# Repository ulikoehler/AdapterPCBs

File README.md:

# AdapterPCBs
Various open hardware adapter PCBs

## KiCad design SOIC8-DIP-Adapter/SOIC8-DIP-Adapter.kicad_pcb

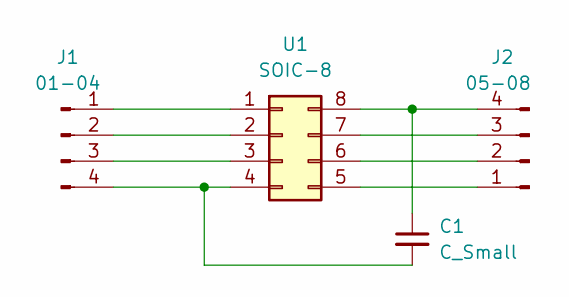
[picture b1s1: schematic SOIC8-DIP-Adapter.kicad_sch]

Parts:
C1: C_Small; C_0603_1608Metric
J1: 01-04; PinHeader_1x04_P2.54mm_Vertical_NoSilkscreen
J2: 05-08; PinHeader_1x04_P2.54mm_Vertical_NoSilkscreen_AllRound
U1: SOIC-8; SO-8_3.9x4.9mm_P1.27mm

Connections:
unnamed: J1.1, U1.1
unnamed: J1.2, U1.2
unnamed: J1.3, U1.3
unnamed: C1.2, J1.4, U1.4
unnamed: J2.1, U1.5
unnamed: J2.2, U1.6
unnamed: J2.3, U1.7
unnamed: C1.1, J2.4, U1.8

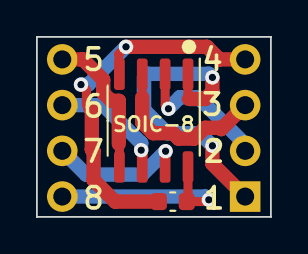
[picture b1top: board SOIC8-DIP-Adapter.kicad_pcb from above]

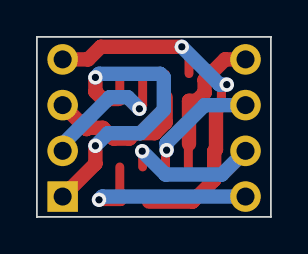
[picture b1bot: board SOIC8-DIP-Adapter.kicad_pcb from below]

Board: 2 copper layers, 13.0 x 10.0 mm, 4 parts (2 on the bottom side), 8 nets.

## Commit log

2022-12-29 Added CERN open hardware license v1.2
2022-12-29 Added SOIC-DIP-Adapter (not finsished yet)
2022-12-29 Finish SOIC-8 adapter
